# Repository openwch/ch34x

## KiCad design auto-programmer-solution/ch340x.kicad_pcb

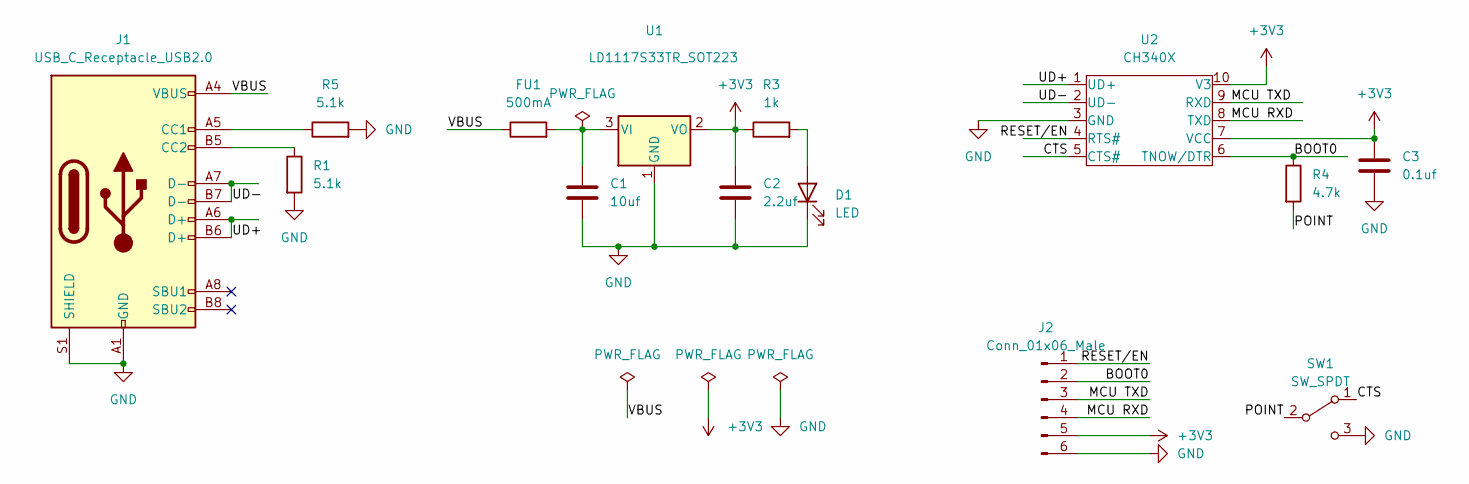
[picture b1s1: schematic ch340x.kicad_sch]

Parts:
C1: 10uf; C_1206_3216Metric_Pad1.33x1.80mm_HandSolder
C2: 2.2uf; C_0603_1608Metric_Pad1.08x0.95mm_HandSolder
C3: 0.1uf; C_0603_1608Metric_Pad1.08x0.95mm_HandSolder
D1: LED; D_0603_1608Metric_Pad1.05x0.95mm_HandSolder
FU1: 500mA; R_0805_2012Metric_Pad1.20x1.40mm_HandSolder
J1: USB_C_Receptacle_USB2.0; USB_C_Receptacle_HRO_TYPE-C-31-M-12
J2: Conn_01x06_Male; PinHeader_1x06_P2.54mm_Vertical
R1, R5: 5.1k; R_0603_1608Metric_Pad0.98x0.95mm_HandSolder
R3: 1k; R_0603_1608Metric_Pad0.98x0.95mm_HandSolder
R4: 4.7k; R_0603_1608Metric_Pad0.98x0.95mm_HandSolder
SW1: SW_SPDT; SW_CuK_OS102011MA1QN1_SPDT_Angled
U1: LD1117S33TR_SOT223; SOT-223-3_TabPin2
U2: CH340X; MSOP-10-1EP_3x3mm_P0.5mm_EP1.68x1.88mm_ThermalVias

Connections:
+3V3: C2.1, C3.1, J2.5, R3.1, U1.2 (VO), U2.7 (VCC), U2.10 (V3)
/BOOT0: J2.2, R4.1, U2.6 (TNOW/DTR)
/CTS: SW1.1 (A), U2.5 (CTS#)
/MCU RXD: J2.4, U2.8 (TXD)
/MCU TXD: J2.3, U2.9 (RXD)
/POINT: R4.2, SW1.2 (B)
/RESET/EN: J2.1, U2.4 (RTS#)
/UD+: J1.A6 (D+), J1.B6 (D+), U2.1 (UD+)
/UD-: J1.A7 (D-), J1.B7 (D-), U2.2 (UD-)
/VBUS: FU1.1, J1.A4 (VBUS), J1.A9 (VBUS), J1.B4 (VBUS), J1.B9 (VBUS); also elsewhere on the board
GND: C1.2, C2.2, C3.2, D1.1 (K), J1.A1 (GND), J1.A12 (GND), J1.B1 (GND), J1.B12 (GND), J1.S1 (SHIELD), J2.6, R1.2, R5.2, SW1.3 (C), U1.1 (GND), U2.3 (GND)
unnamed 11: C1.1, FU1.2, U1.3 (VI); also elsewhere on the board
unnamed: D1.2 (A), R3.2
unnamed: J1.A5 (CC1), R5.1
unnamed: J1.B5 (CC2), R1.1

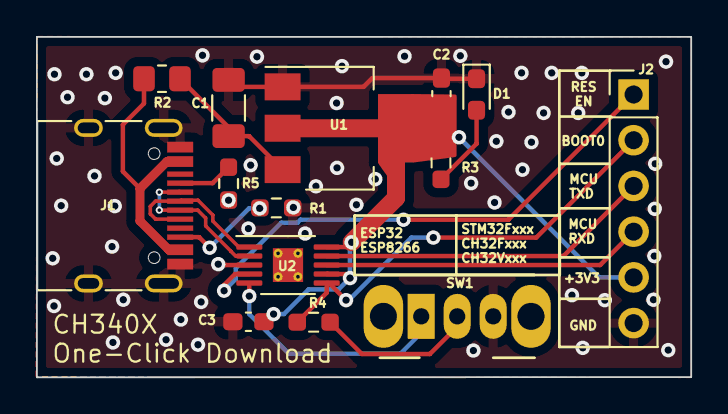
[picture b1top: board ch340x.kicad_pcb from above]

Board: 2 copper layers, 36.4 x 18.9 mm, 14 parts (0 on the bottom side), 15 nets.

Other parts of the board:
R2: 500mA; R_0805_2012Metric_Pad1.20x1.40mm_HandSolder

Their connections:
/VBUS: R2.1; also elsewhere on the board
unnamed 11: R2.2; also elsewhere on the board

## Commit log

2022-01-17 CH340 series USB to UART chips
2022-01-17 Add files via upload
    WCH USB configuration Tool CH34xsercfg instructions
2022-01-17 ch9102 sdk_hdk
2022-01-17 CH34x datasheet-EN
2022-02-18 update CH348DS1_EN_1B
2022-03-14 Create driver
